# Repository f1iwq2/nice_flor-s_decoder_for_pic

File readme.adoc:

Nice flor-s / Came / CARDIN S449 / Somfy RTS / EV1527 /PT2260 remote decoder receiver for pic
=============================================================================================

Programme pic pour décoder les protocoles des télécommandes Nice-florS, CAME, EV1527, PT2260, Cardin S449 et Somfy RTS.
Fobloqs n'est pas terminé.
Le projet est composé d'un PIC 18F26K80 à 16 MHz (x4 par pll = 64 MHz)
L'eprom interne contient le fichier ki.bin ainsi que les télécommandes apprises.
L'eprom externe de 128Ko contient le fichier codes.bin
Le platine électronique est faite en Kicad, répertoire "telecommande".
Le logiciel est fait avec MPLAB XIDE, repertoire "telecommande.X".
Utiliser la directive francais pour basculer en français pour le dialogues UART (230400 bauds par défaut)
Came utilise le protocole radio OOK, code fixe.
NiceFlorS utilise le protocole radio ASK, code roulant.
Cardin utilise le protocole radio FSK, code roulant.
Utilisez le récepteur adéquat. Ne brancher qu'un seul récepteur sur la platine.
RXB6, RFM210LCF-A = ASK et OOK.
RXB15 = FSK
documentation dans le fichier pdf.

Taper ? [enter] dans le terminal pour afficher le menu.

Pic program to decode Nice-florS, CAME, EV1527, Cardin S449, and SOMFY RTS remote devices.
Fobloqs is not completed.
This project is made with a PIC 18F26K80 at 16 MHz (x4 with pll = 64 MHz)
Internal eprom contains the ki.bin file, and also learnt remotes.
External 128Kb eprom contains codes.bin file. 
The electronic board is made with Kicad, "telecommande" directory.
The software is made with MPLAB XIDE, "telecommande.X" directory.
Use english directive to switch to english UART dialogs (230400 bauds default).

CAME use OOK radio protocol. 
NiceFlorS use ASK radio protocol, rolling code.
Cardin use FSK radio protocol
Use the correct receiver. Plug only a single receiver on the board.
RXB6, RFM210LCF-A = ASK and OOK.
RXB15 = FSK
Documentation in pdf file.

Type in ? [enter] to display the menu.

The projet a été inspiré par :
This project was inspired from :
https://github.com/Jev1337/NiceFlor-Encoder

image::photo.jpg[]
image::telecommande.jpg[]

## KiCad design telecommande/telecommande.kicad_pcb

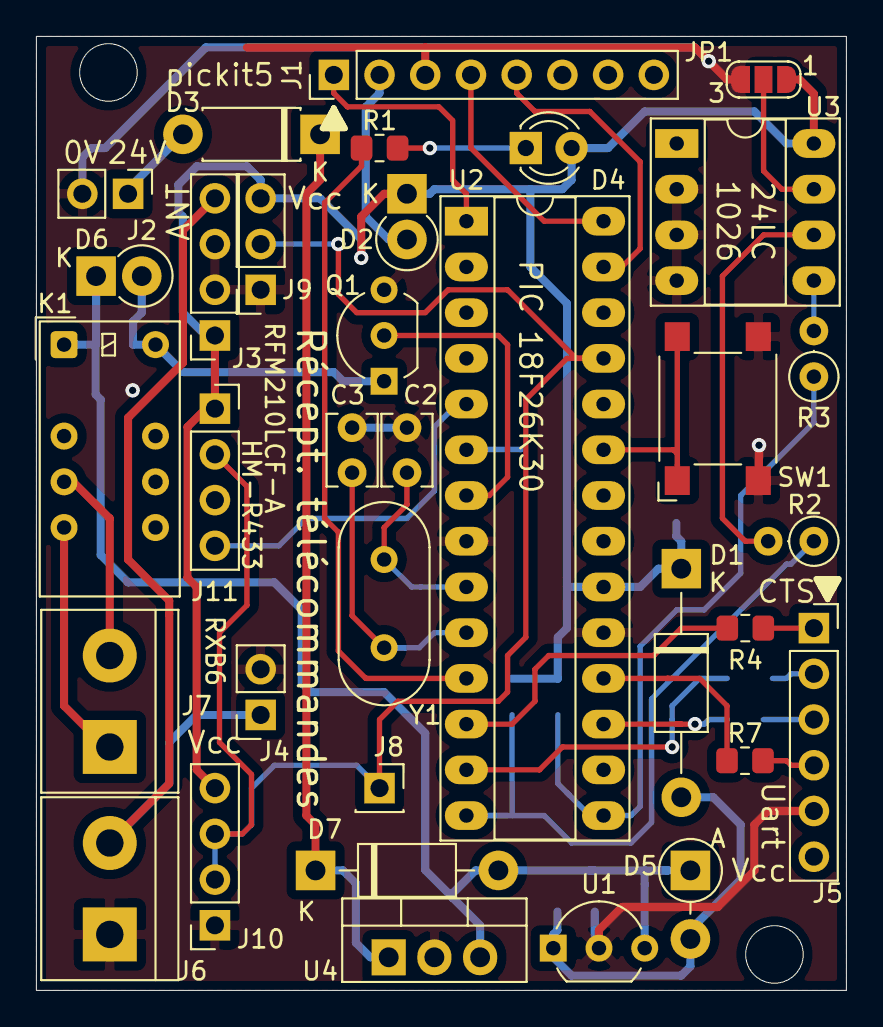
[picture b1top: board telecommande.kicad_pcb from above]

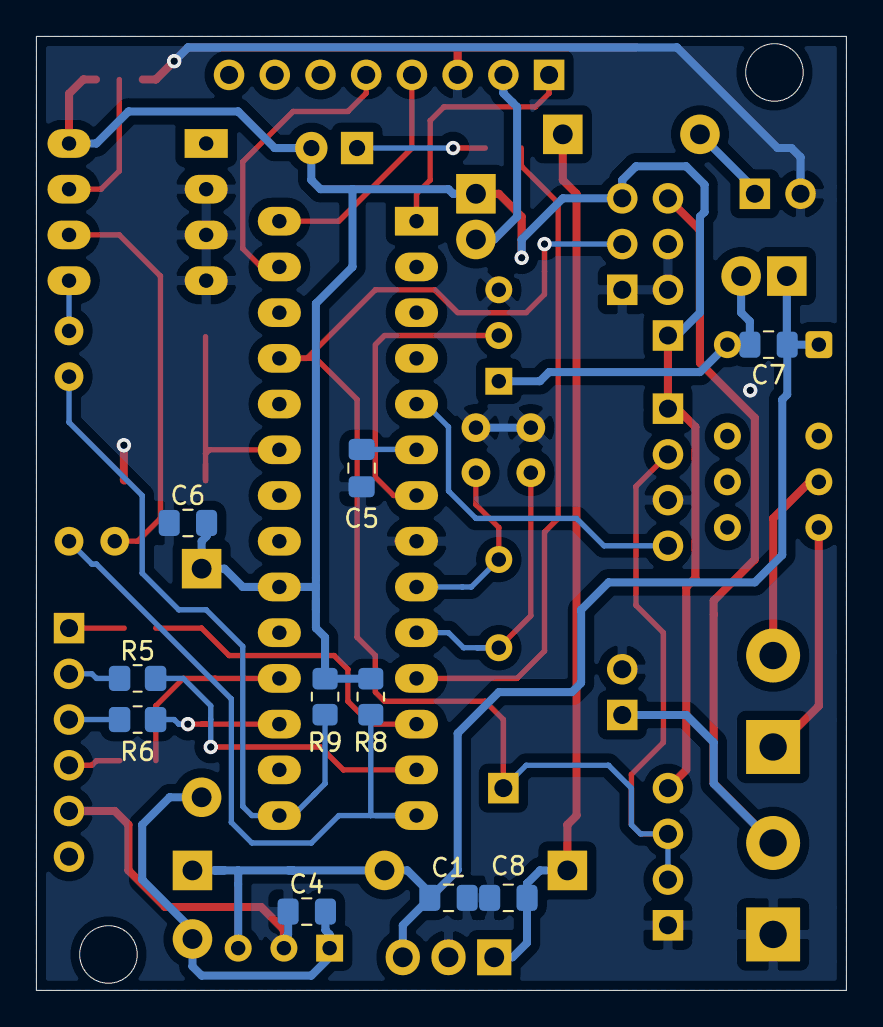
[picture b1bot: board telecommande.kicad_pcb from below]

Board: 2 copper layers, 45.0 x 53.0 mm, 46 parts (10 on the bottom side), 36 nets.

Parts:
C1, C4, C5, C6, C7, C8: 100nF; C_0805_2012Metric_Pad1.18x1.45mm_HandSolder
C2, C3: 15pF; C_Disc_D3.8mm_W2.6mm_P2.50mm
D1: 1N4004; D_DO-41_SOD81_P12.70mm_Horizontal
D2, D6: 1N4004; D_DO-41_SOD81_P2.54mm_Vertical_KathodeUp
D3: 1N4004; D_DO-41_SOD81_P7.62mm_Horizontal
D4: LED; LED_D3.0mm
D5: 1N4004; D_DO-41_SOD81_P3.81mm_Vertical_AnodeUp
D7: 1N4004; D_DO-41_SOD81_P10.16mm_Horizontal
H1, H2: MountingHole; MountingHole_3.2mm_M3
J1: Conn_01x08_Male; PinHeader_1x08_P2.54mm_Vertical
J2: Conn_01x02_Male; PinHeader_1x02_P2.54mm_Vertical
J3, J10, J11: Conn_01x04_Female; PinSocket_1x04_P2.54mm_Vertical
J4: Conn_01x02_Female; PinSocket_1x02_P2.54mm_Vertical
J5: Conn_01x06_Male; PinSocket_1x06_P2.54mm_Vertical
J6, J7: Screw_Terminal_01x02; TerminalBlock_bornier-2_P5.08mm
J8: Conn_01x01_Male; PinSocket_1x01_P2.54mm_Vertical
J9: Conn_01x03_Female; PinSocket_1x03_P2.54mm_Vertical
JP1: SolderJumper_3_Open; SolderJumper-3_P1.3mm_Open_RoundedPad1.0x1.5mm_NumberLabels
K1: ATX203; Relay_DPDT_Kemet_EC2
Q1: BS170; TO-92_Inline_Wide
R1: 330; R_0805_2012Metric_Pad1.20x1.40mm_HandSolder
R2, R3: 330; R_Axial_DIN0207_L6.3mm_D2.5mm_P2.54mm_Vertical
R4, R5, R6, R7: 90; R_0805_2012Metric_Pad1.20x1.40mm_HandSolder
R8, R9: 8,2k; R_0805_2012Metric_Pad1.20x1.40mm_HandSolder
SW1: SW_MEC_5E; SW_SPST_Omron_B3FS-101xP
U1: L78L05_TO92; TO-92_Inline_Wide
U2: PIC18F26K80_ISS; DIP-28_W7.62mm_Socket_LongPads
U3: 24LC1026-I_P; DIP-8_W7.62mm_Socket_LongPads
U4: L7812; TO-220-3_Vertical
Y1: Crystal 16MHz; Crystal_HC18-U_Vertical

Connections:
/12VR: C1.1, C7.1, D5.1, D6.1, D7.2, K1.1, U1.3, U4.3
/ANT: J3.4, J4.1, J6.2
/Bp1: SW1.1, SW1.2, U2.23
/CTS: J5.2, R5.1
/Enable: J11.4, U2.5
/LED: R1.2, U2.11
/MCLR: J1.1, U2.1
/PGC: J1.5, U2.27
/PGD: J1.4, U2.28
/RTS: J5.1, R4.1
/RX: J8.1, J9.2, J10.2, J10.3, J11.2, U2.25
/RX1: J5.4, R7.1
/Rel1: Q1.2, U2.7
/SCL: R2.1, R8.2, U2.14
/SDA: R3.1, R9.2, U2.15
/TVDD: D2.2, J1.2
/TX1: J5.3, R6.1
/VCC: C4.1, D1.2, D5.2, U1.1
/VDD: C6.1, D1.1, D2.1, D4.2, J3.1, J9.3, J10.4, J11.1, JP1.1, R8.1, R9.1, U2.20, U3.8
GND: C1.2, C2.2, C3.2, C4.2, C5.2, C6.2, C8.2, J1.3, J2.2, J3.2, J3.3, J4.2, J5.5, J6.1, J9.1, J10.1, J11.3, JP1.3, Q1.3, SW1.3, SW1.4, U1.2, U2.8, U2.19, U3.2, U3.3, U3.4, U4.2
unnamed: C2.1, U2.9, Y1.1
unnamed: C3.1, U2.10, Y1.2
unnamed: C5.1, U2.6
unnamed: C7.2, D6.2, K1.12, Q1.1
unnamed: C8.1, D3.1, D7.1, U4.1
unnamed: D3.2, J2.1
unnamed: D4.1, R1.1
unnamed: J7.1, K1.5
unnamed: J7.2, K1.4
unnamed: JP1.2, U3.7
unnamed: R2.2, U3.6
unnamed: R3.2, U3.5
unnamed: R4.2, U2.12
unnamed: R5.2, U2.13
unnamed: R6.2, U2.17
unnamed: R7.2, U2.18

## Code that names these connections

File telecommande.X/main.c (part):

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#define english     0    // choose your language

#define led     RC0     // sortie
#define rts     RC1     // sortie - not used : UART protocole rts/cts - vers CTS PC : bloque l'envoi du PC
#define cts     RC2     // entrée - not used : UART protocole rts/cts - de PC : bloque l'envoi vers le PC
#define enable  RA3     // enable récepteur HM-R-433 ou autre qui ont une entrée enable
#define rel1    RA5     // commande bobine du relais / relay coil command
#define MAX_COMMAND_LEN       8U
#define LINEFEED_CHAR         (uint8_t)'\n'
#define CARRIAGERETURN_CHAR   (uint8_t)'\r'
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      printf(" ok");
      // coller le relais 1 seconde
      // relay 1 second on
      rel1=1;
      led=0;
      __delay_ms(1000);
      rel1=0;
      led=1;
    }
    else 
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{
  SYSTEM_Initialize();
  enable=0;
  rel1=0;   // relais non collé
  erreur=0;
    
  // If using interrupts in PIC18 High/Low Priority Mode you need to enable the Global High and Low Interrupts 
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  {
    
    /* essai rts
    rts=1;
    __delay_ms(200);
    rts=0;
    __delay_ms(200);
        
    // essai cts
    //if (cts==1) led=1; else led=0;
    */
      
    if (!RB2) // bouton appuyé
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
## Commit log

2025-05-31 V1.0
2025-06-06 add came
2025-06-09 up0906
2025-06-09 urm2
2025-06-11 upds
2025-07-05 07/05/2025
2025-07-06 06/07/2025
2025-07-11 11/07/2025
2025-07-12 12/07/2025
2025-07-13 13/07/2025
2025-07-15 15/07/2025
2025-07-18 18/07/2025
2025-08-08 8/8/2025
2025-08-11 photo
2025-11-09 update SCT2260
